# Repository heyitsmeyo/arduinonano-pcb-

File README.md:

# arduinonano-pcb-
a custom arduino nano pcb desigb 

# if you like the project , you can donate us for more : 

    https://ko-fi.com/heyitsmeyo

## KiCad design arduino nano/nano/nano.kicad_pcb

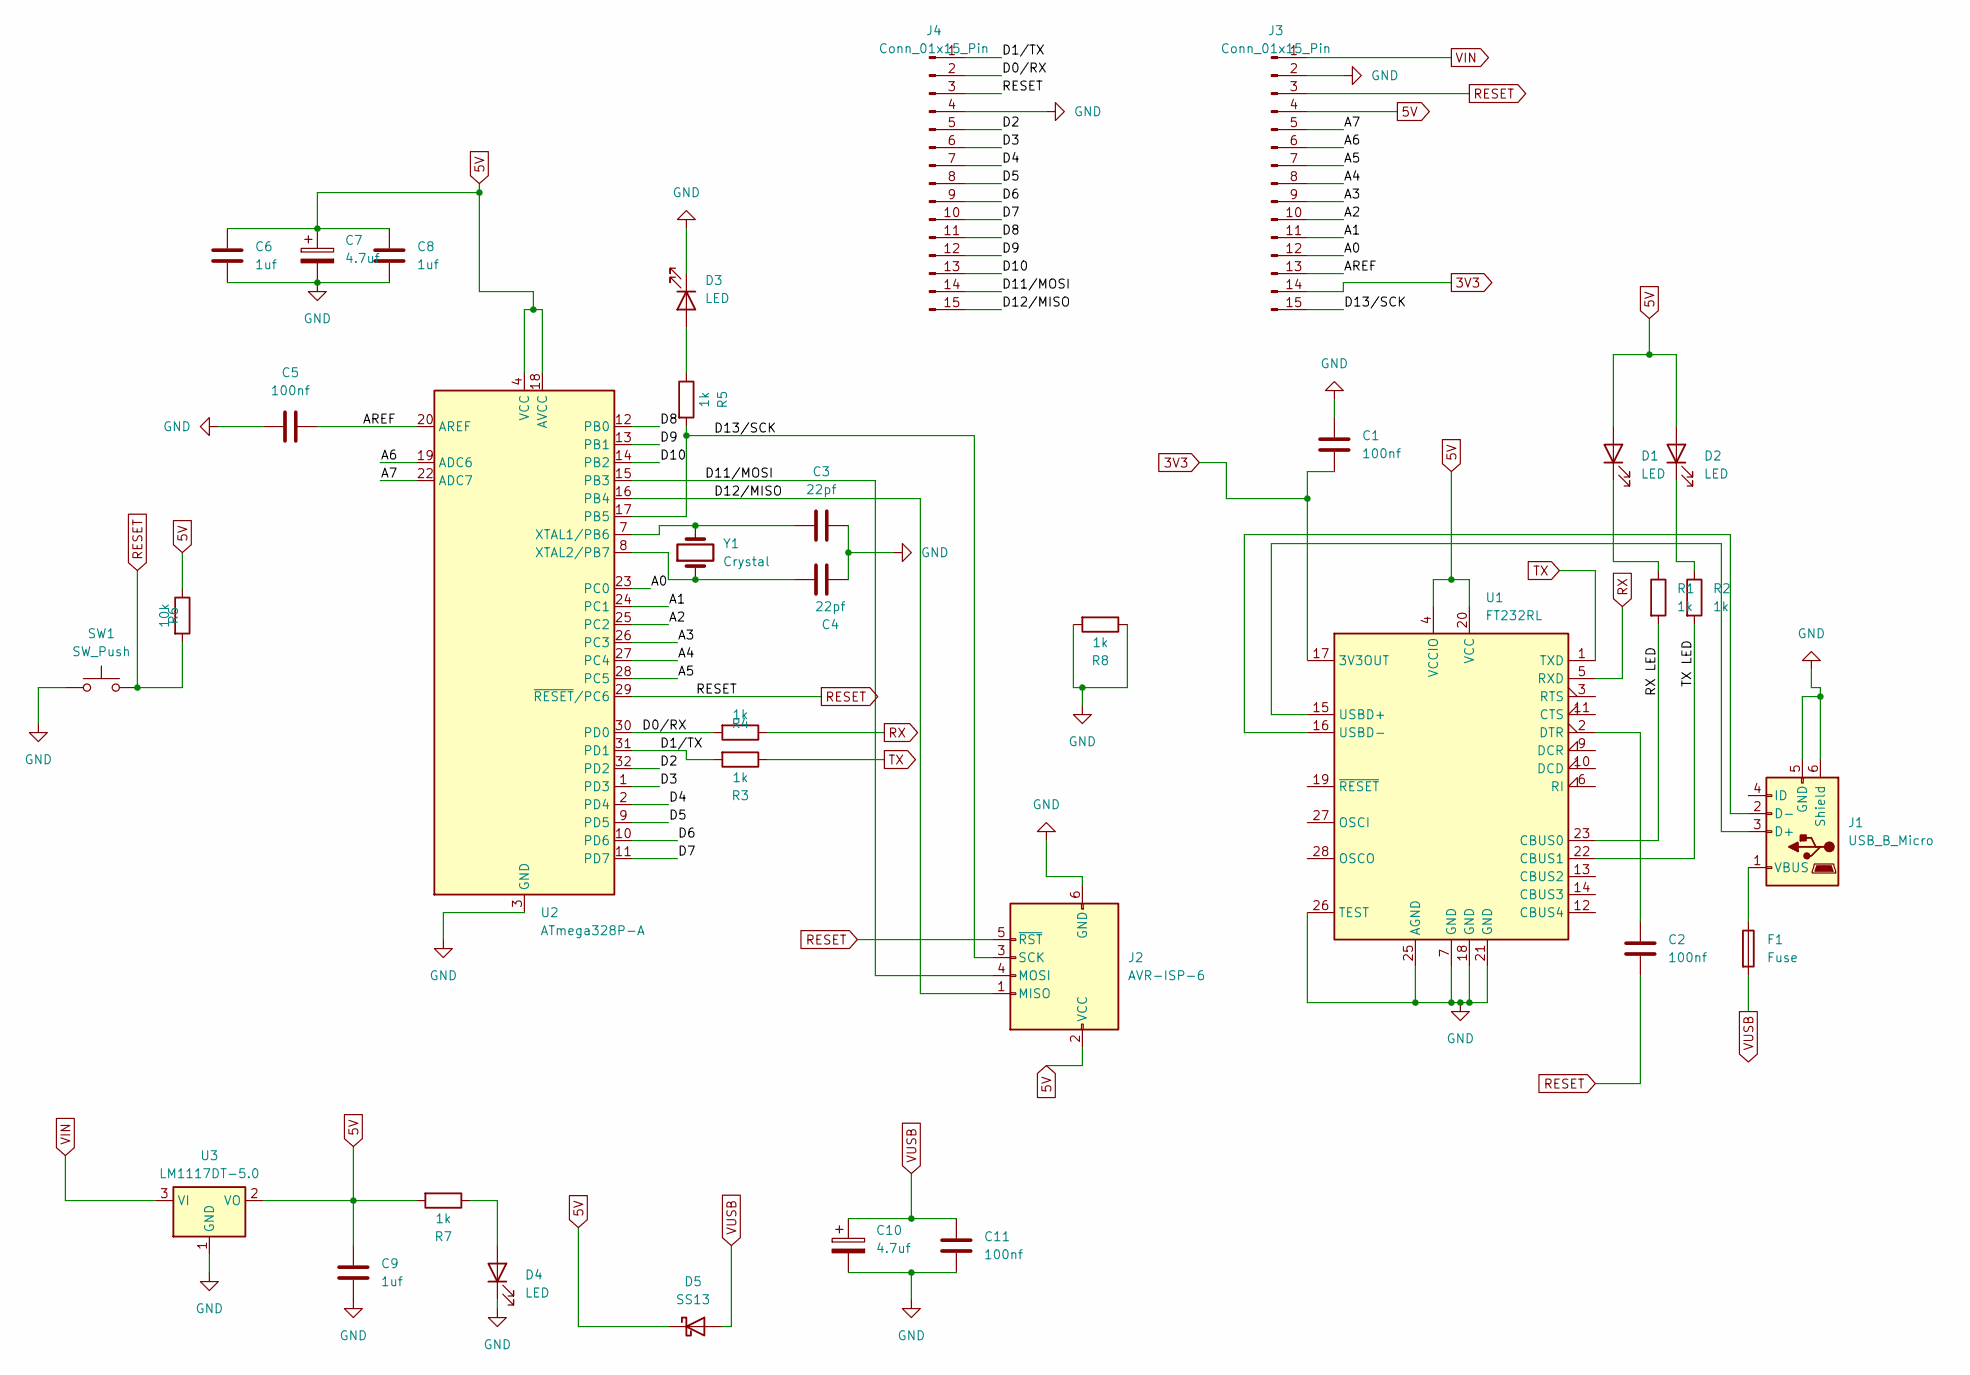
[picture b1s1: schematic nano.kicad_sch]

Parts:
C1, C2, C5, C11: 100nf; C_0201_0603Metric
C3, C4: 22pf; C_0201_0603Metric
C6, C8, C9: 1uf; C_0201_0603Metric
C7, C10: 4.7uf; CP_Elec_4x5.8
D1, D2, D3, D4: LED; LED_0603_1608Metric
D5: SS13; D_SMA
F1: Fuse; R_0603_1608Metric
J1: USB_B_Micro; USB_Micro-B_Amphenol_10103594-0001LF_Horizontal
J2: AVR-ISP-6; PinHeader_2x03_P2.54mm_Vertical_SMD
J3, J4: Conn_01x15_Pin; PinHeader_1x15_P2.54mm_Vertical
R1, R2, R3, R4, R5, R7, R8: 1k; R_0201_0603Metric
R6: 10k; R_0201_0603Metric
SW1: SW_Push; SW_Tactile_SPST_NO_Straight_CK_PTS636Sx25SMTRLFS
U1: FT232RL; SSOP-28_3.9x9.9mm_P0.635mm
U2: ATmega328P-A; TQFP-32_7x7mm_P0.8mm
U3: LM1117DT-5.0; TO-252-3_TabPin2
Y1: Crystal; Crystal_SMD_Abracon_ABM3-2Pin_5.0x3.2mm

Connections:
3V3: C1.2, J3.14, U1.17 (3V3OUT)
5V: C6.2, C7.1, C8.2, C9.2, D1.2 (A), D2.2 (A), D5.1 (K), J2.2 (VCC), J3.4, R6.1, R7.2, U1.4 (VCCIO), U1.20 (VCC), U2.4 (VCC), U2.6 (VCC), U2.18 (AVCC), U3.2 (VO)
/A0: J3.12, U2.23 (PC0)
/A1: J3.11, U2.24 (PC1)
/A2: J3.10, U2.25 (PC2)
/A3: J3.9, U2.26 (PC3)
/A4: J3.8, U2.27 (PC4)
/A5: J3.7, U2.28 (PC5)
/A6: J3.6, U2.19 (ADC6)
/A7: J3.5, U2.22 (ADC7)
/AREF: C5.2, J3.13, U2.20 (AREF)
/D0/RX: J4.2, R4.2, U2.30 (PD0)
/D1/TX: J4.1, R3.2, U2.31 (PD1)
/D2: J4.5, U2.32 (PD2)
/D3: J4.6, U2.1 (PD3)
/D4: J4.7, U2.2 (PD4)
/D5: J4.8, U2.9 (PD5)
/D6: J4.9, U2.10 (PD6)
/D7: J4.10, U2.11 (PD7)
/D8: J4.11, U2.12 (PB0)
/D9: J4.12, U2.13 (PB1)
/D10: J4.13, U2.14 (PB2)
/D11/MOSI: J2.4 (MOSI), J4.14, U2.15 (PB3)
/D12/MISO: J2.1 (MISO), J4.15, U2.16 (PB4)
/D13/SCK: J2.3 (SCK), J3.15, R5.2, U2.17 (PB5)
/RX LED: R1.2, U1.23 (CBUS0)
/TX LED: R2.2, U1.22 (CBUS1)
GND: C1.1, C3.2, C4.2, C5.1, C6.1, C7.2, C8.1, C9.1, C10.2, C11.2, D3.1 (K), D4.1 (K), J1.5 (GND), J1.6 (Shield), J2.6 (GND), J3.2, J4.4, R8.1, R8.2, SW1.1, U1.7 (GND), U1.18 (GND), U1.21 (GND), U1.25 (AGND), U1.26 (TEST), U2.3 (GND), U2.5 (GND), U2.21 (GND), U3.1 (GND)
unnamed: D1.1 (K), R1.1
unnamed: D2.1 (K), R2.1
unnamed: D3.2 (A), R5.1
unnamed: D4.2 (A), R7.1
unnamed: J1.3 (D+), U1.15 (USBD+)
unnamed: J1.2 (D-), U1.16 (USBD-)
unnamed: F1.1, J1.1 (VBUS)
unnamed: C2.1, U1.2 (DTR)
unnamed 36: C3.1, U2.7 (XTAL1/PB6), Y1.2; also elsewhere on the board
unnamed 37: C4.1, U2.8 (XTAL2/PB7), Y1.1; also elsewhere on the board
RESET: C2.2, J2.5 (~RST), J3.3, J4.3, R6.2, SW1.2, U2.29 (~RESET/PC6)
RX: R4.1, U1.5 (RXD)
TX: R3.1, U1.1 (TXD)
VIN: J3.1, U3.3 (VI)
VUSB: C10.1, C11.1, D5.2 (A), F1.2

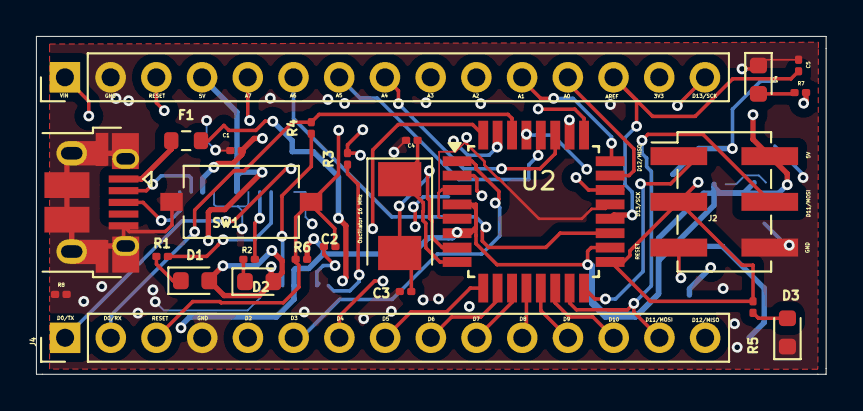
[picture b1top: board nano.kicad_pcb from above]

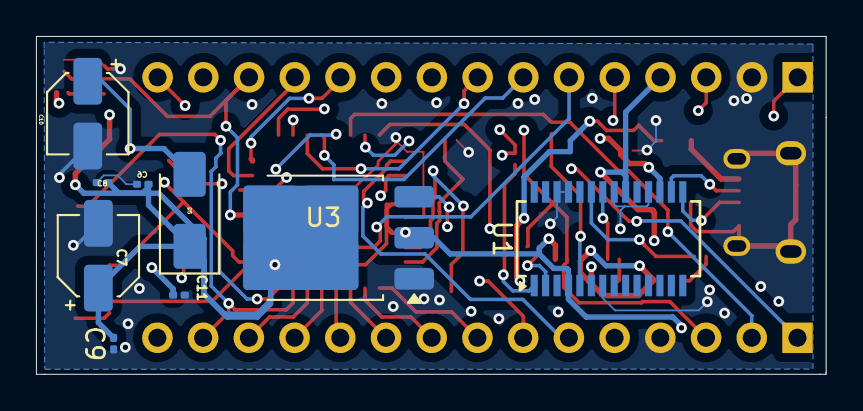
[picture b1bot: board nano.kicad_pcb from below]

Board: 4 copper layers, 43.9 x 18.8 mm, 34 parts (9 on the bottom side), 43 nets.

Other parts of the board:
Oscillator 16 MHz: Crystal; Crystal_SMD_Abracon_ABM3-2Pin_5.0x3.2mm

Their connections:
unnamed 36: Oscillator 16 MHz.2; also elsewhere on the board
unnamed 37: Oscillator 16 MHz.1; also elsewhere on the board
